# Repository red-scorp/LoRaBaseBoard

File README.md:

# LoRaBaseBoard

LoRa Base Board for popular Hoperf's RFM95/96/97/98 modules.

One day I wanted to play with LoRa in sender-receiver setup.
What I have fount there are a lot of SMD-mountable modules available but no modules suitable for common prototyping breadboards.
Here I've tried to create a user friendly way to use commonly available LoRa modules.

## LoRaBaseBoard

Simple adapted board intended to be used with variety of RFM LoRa radio modules and being used for HW prototyping.

Preview:

[Schematics in PDF format](doc/LoRaBaseBoard.pdf)

Features:

- generic board for RFM radio modules
- compatible with common breadboards and prototyping boards (2.54mm raster)

CAM files are available.

## LoRaAdapter

This adapter board is meant to be a drop-in replacement for NRF24L01 modules.

Preview:

[Schematics in PDF format](doc/LoRaAdapter.pdf)

Features:

- generic board for RFM95/96/97/98 LoRa radio modules
- compatible with NRF24L01 pinout

CAM files are available.

## BOM

Bill Of Materials is currently available only for LCSC Electronic Components Distributor, which is probably cheapest anyway.

### LCSC BOM

|Designator  |Part/Value  |Package/Footprint     |LCSC # |
|------------|------------|----------------------|-------|
|C1          |Cap. 100nF  |0603                  |C14663 |
|C2          |Cap. 22uF   |1206                  |C5672  |
|A1          |SMA conn.   |                      |C496551|
|A2          |U.FL conn.  |SMD                   |C88374 |

All passive components are optional!

## How to help

Your contributions as code, resources, or finances are welcome! Please contact me directly via email at andriy.golovnya@gmail.com or through my [GitHub profile](https://github.com/red-scorp).

If you'd like to make a financial contribution, you can donate via [PayPal](http://paypal.me/redscorp) or [Ko-Fi](http://ko-fi.com/redscorp). Your support is greatly appreciated.

Thanks in advance!

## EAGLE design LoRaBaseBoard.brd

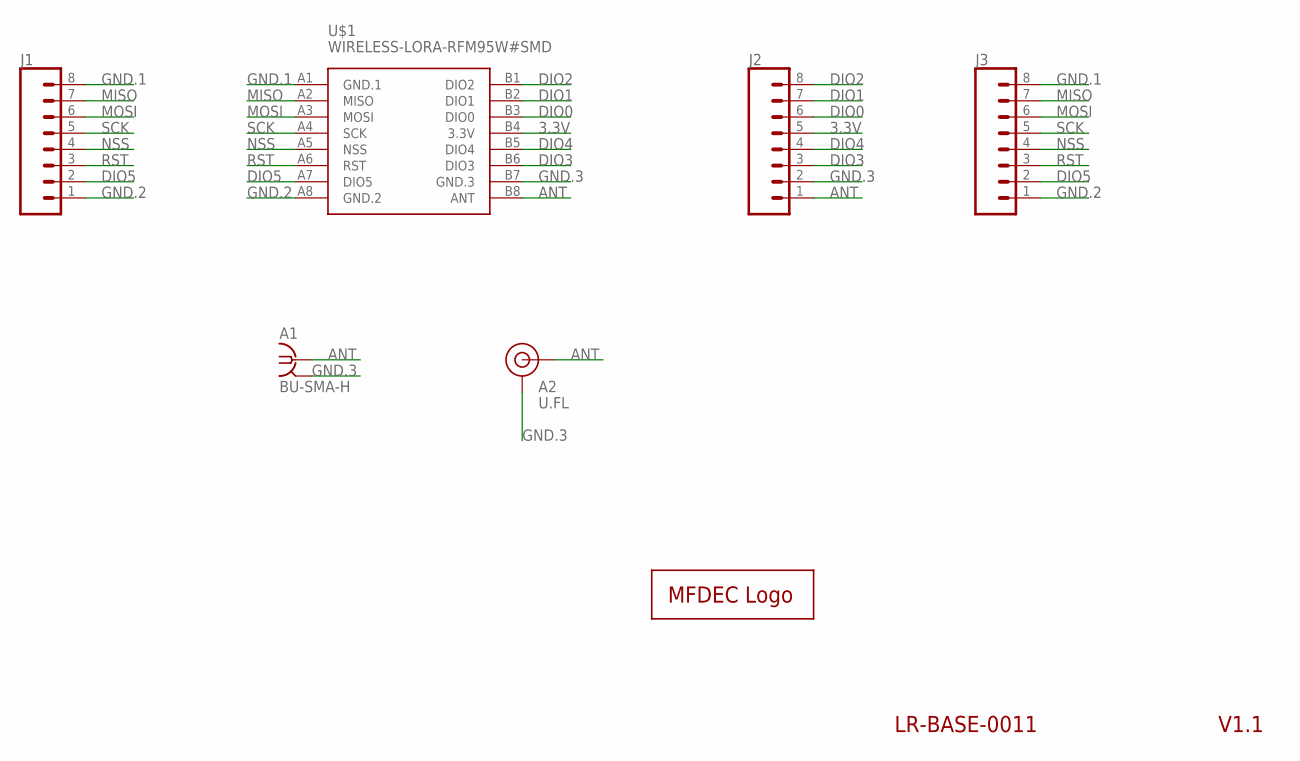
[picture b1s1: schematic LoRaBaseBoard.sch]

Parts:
A1: BU-SMA-H
A2: U.FL
J1, J2, J3: CONN_08NO_SILK_FEMALE_PTH; 1X08_NO_SILK
LOGO1: MFDECLOGO_SQ_8MM; MFDEC_SQ_8MM
U$1: WIRELESS-LORA-RFM95W#SMD

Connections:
3.3V: J2.5, U$1.B4 (3.3V)
ANT: A1.1, A2.FEED (SIGNAL), J2.1, U$1.B8 (ANT)
DIO0: J2.6, U$1.B3 (DIO0)
DIO1: J2.7, U$1.B2 (DIO1)
DIO2: J2.8, U$1.B1 (DIO2)
DIO3: J2.3, U$1.B6 (DIO3)
DIO4: J2.4, U$1.B5 (DIO4)
DIO5: J1.2, J3.2, U$1.A7 (DIO5)
GND.1: J1.8, J3.8, U$1.A1 (GND.1)
GND.2: J1.1, J3.1, U$1.A8 (GND.2)
GND.3: A1.2, A1.3 (2), A1.4 (2), A1.5 (2), A2.1 (GND), A2.2 (GND), J2.2, U$1.B7 (GND.3)
MISO: J1.7, J3.7, U$1.A2 (MISO)
MOSI: J1.6, J3.6, U$1.A3 (MOSI)
NSS: J1.4, J3.4, U$1.A5 (NSS)
RST: J1.3, J3.3, U$1.A6 (RST)
SCK: J1.5, J3.5, U$1.A4 (SCK)

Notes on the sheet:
V1.1
LR-BASE-0011

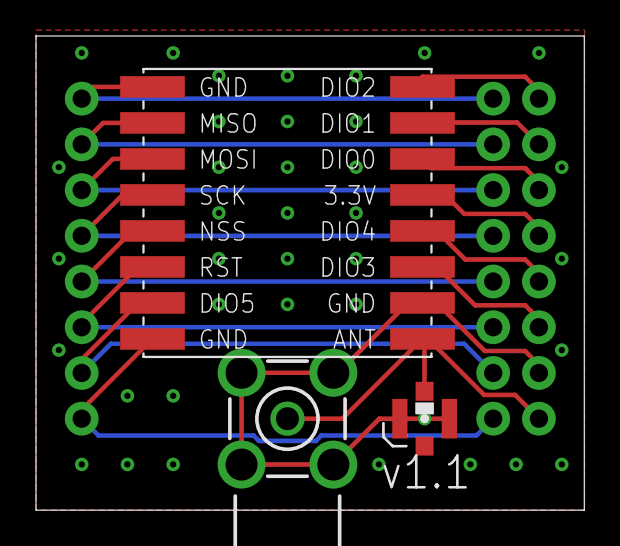
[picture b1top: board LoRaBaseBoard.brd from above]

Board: 2 copper layers, 30.5 x 26.3 mm, 7 parts (1 on the bottom side), 16 nets.

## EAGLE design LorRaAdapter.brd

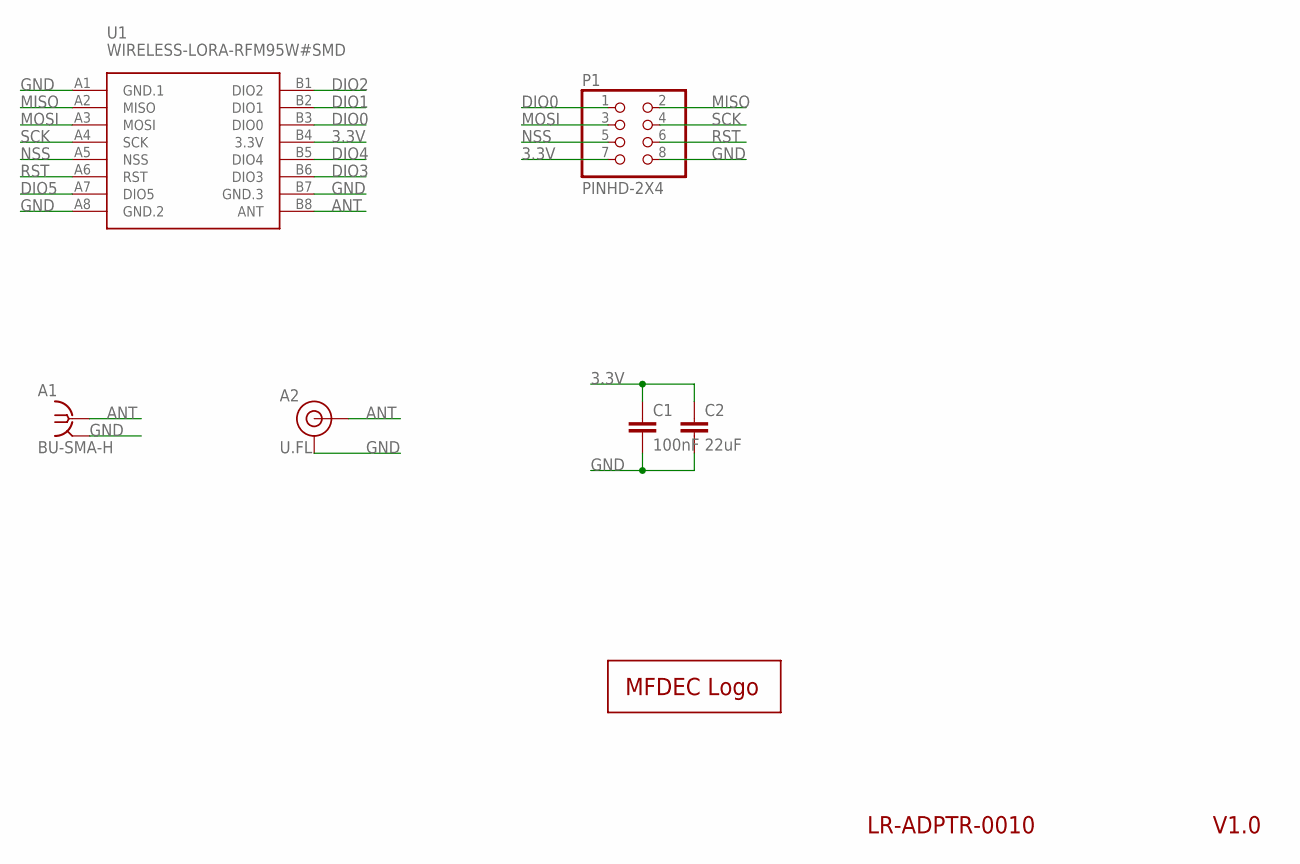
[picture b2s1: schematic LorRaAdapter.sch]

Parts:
A1: BU-SMA-H
A2: U.FL
C1: 100nF; C0603
C2: 22uF; C1206
LOGO1: MFDECLOGO_SQ_5MM; MFDEC_SQ_5MM
P1: PINHD-2X4; 2X04
U1: WIRELESS-LORA-RFM95W#SMD

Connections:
3.3V: C1.1, C2.1, P1.7, U1.B4 (3.3V)
ANT: A1.1, A2.FEED (SIGNAL), U1.B8 (ANT)
DIO0: P1.1, U1.B3 (DIO0)
DIO1: U1.B2 (DIO1)
DIO2: U1.B1 (DIO2)
DIO3: U1.B6 (DIO3)
DIO4: U1.B5 (DIO4)
DIO5: U1.A7 (DIO5)
GND: A1.2, A1.3 (2), A1.4 (2), A1.5 (2), A2.1 (GND), A2.2 (GND), C1.2, C2.2, P1.8, U1.A1 (GND.1), U1.A8 (GND.2), U1.B7 (GND.3)
MISO: P1.2, U1.A2 (MISO)
MOSI: P1.3, U1.A3 (MOSI)
NSS: P1.5, U1.A5 (NSS)
RST: P1.6, U1.A6 (RST)
SCK: P1.4, U1.A4 (SCK)

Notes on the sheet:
V1.0
LR-ADPTR-0010

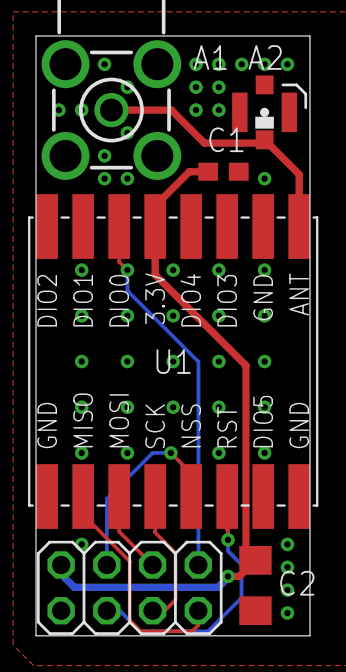
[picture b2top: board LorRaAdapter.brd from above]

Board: 2 copper layers, 15.2 x 33.3 mm, 7 parts (1 on the bottom side), 9 nets.

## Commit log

2020-09-17 Initial state of the repository
2020-09-19 Add Midnight Fog logos
2020-12-11 Added board ids. Changed some visuals.
2020-12-11 Generated new CAM.
2020-12-19 Added PDF schematics.
2020-12-19 Added PNG preview images.
2020-12-19 Renamed antenna connectors.
2020-12-19 Added README.
2020-12-19 Renamed files
2020-12-19 Generated new PDF schematics.
2020-12-26 Moved some traces.
2020-12-26 Generated new PNG preview image.
2021-01-13 Fixed description
2021-12-05 cleanup.
2022-01-24 Added Ko-Fi link
2022-03-14 Fixed fill distance. Generated CAM files. Generated PNG preview.
2022-03-14 Changed soldermask color to green. Generated PNG preview.
2022-03-14 Generated PDF schematics.
2023-08-28 Updated 'How to help' section.

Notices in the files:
parts and their libraries:
SparkFun-Connectors: Licensing: Creative Commons ShareAlike 4.0 International - https://creativecommons.org/licenses/by-sa/4.0
diy-modules: Released under the Creative Commons Attribution 4.0 International License: http://creativecommons.org/licenses/by/4.0
